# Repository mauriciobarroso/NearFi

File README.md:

# NearFi
NearFi is a proximity Wi-Fi repeater based on ESP32-S2-WROOM module (ESP32-S2), ESP IDF framework and KiCAD

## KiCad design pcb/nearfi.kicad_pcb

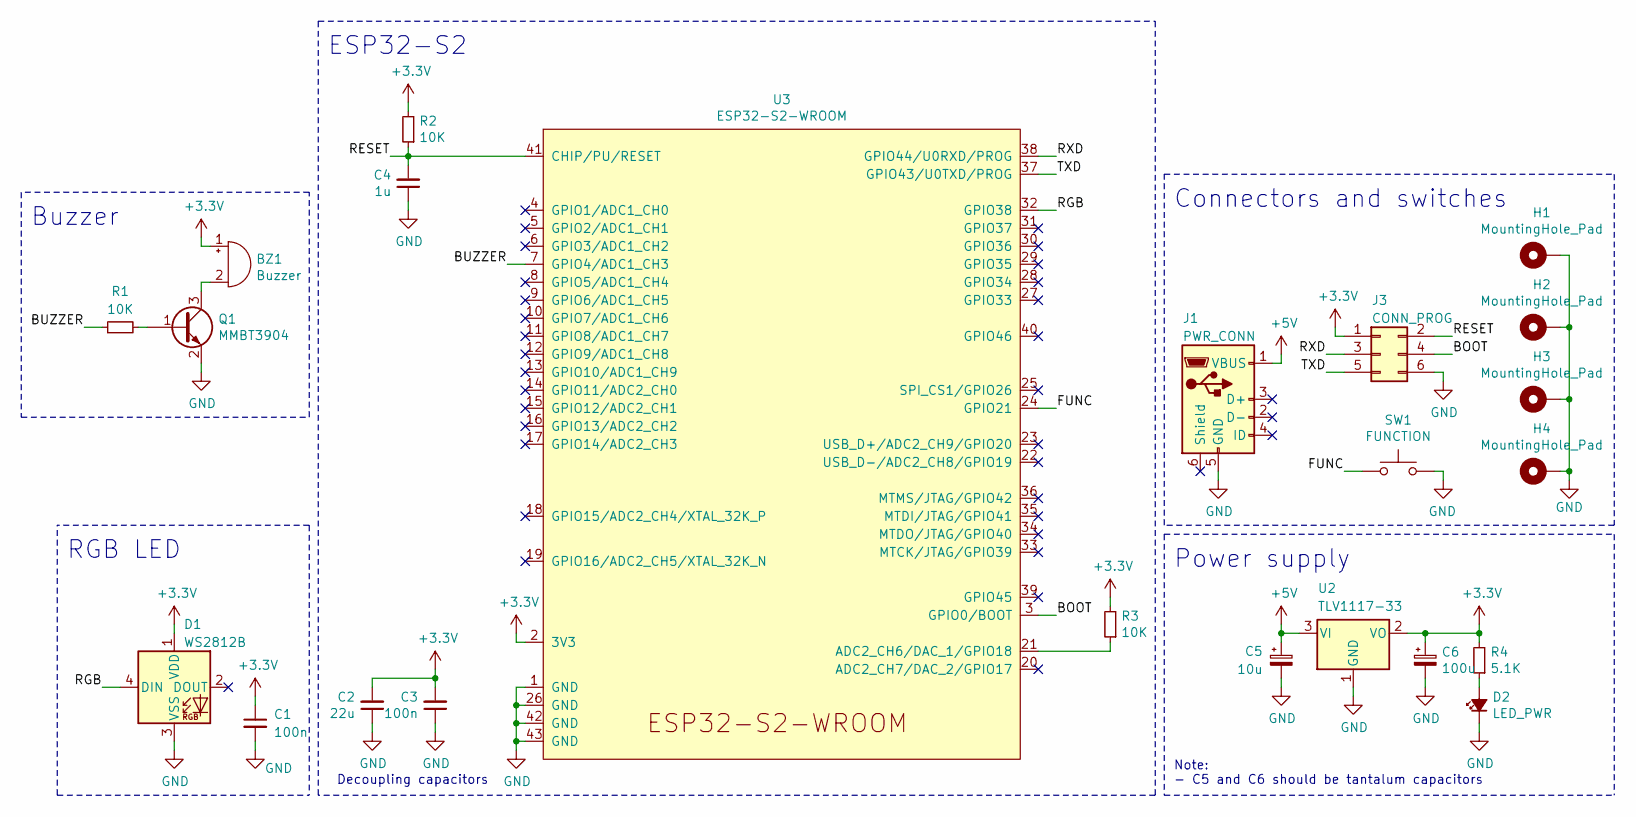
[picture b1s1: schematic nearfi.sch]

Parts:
BZ1: Buzzer; Buzzer_12x9.5RM7.6
C1, C3: 100n; C_0805_2012Metric_Pad1.18x1.45mm_HandSolder; LCSC C49678
C2: 22u; C_0805_2012Metric_Pad1.18x1.45mm_HandSolder; LCSC C45783
C4: 1u; C_0805_2012Metric_Pad1.18x1.45mm_HandSolder; LCSC C28323
C5: 10u; CP_EIA-3216-18_Kemet-A_Pad1.58x1.35mm_HandSolder; LCSC C7171
C6: 100u; CP_EIA-3528-21_Kemet-B_Pad1.50x2.35mm_HandSolder; LCSC C16133
D1: WS2812B; LED_WS2812B_PLCC4_5.0x5.0mm_P3.2mm; LCSC C2761795
D2: LED_PWR; LED_0805_2012Metric_Castellated; LCSC C84256
H1, H2, H3, H4: MountingHole_Pad; MountingHole_3.2mm_M3_Pad_Via
J1: PWR_CONN; USB_Micro-B_Molex_47346-0001; LCSC C132560
J3: CONN_PROG; PinHeader_2x03_P2.54mm_Vertical
Q1: MMBT3904; SOT-23; LCSC C20526
R1, R2, R3: 10K; R_0805_2012Metric_Pad1.20x1.40mm_HandSolder; LCSC C17414
R4: 5.1K; R_0805_2012Metric_Pad1.20x1.40mm_HandSolder; LCSC C27834
SW1: FUNCTION; SW_Tactile_SPST_Angled_PTS645Vx31-2LFS
U2: TLV1117-33; SOT-223-3_TabPin2; LCSC C37359
U3: ESP32-S2-WROOM; LCSC C967025

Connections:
+3V3: BZ1.1 (-), C1.1, C2.2, C3.2, C6.1, D1.1 (VDD), J3.1, R2.2, R3.2, R4.2, U2.2 (VO), U3.2 (3V3)
+5V: C5.1, J1.1 (VBUS), U2.3 (VI)
/BOOT: J3.4, U3.3 (GPIO0/BOOT)
/BUZZER: R1.1, U3.7 (GPIO4/ADC1_CH3)
/FUNC: SW1.2, U3.24 (GPIO21)
/RESET: C4.2, J3.2, R2.1, U3.41 (CHIP/PU/RESET)
/RGB: D1.4 (DIN), U3.32 (GPIO38)
/RXD: J3.3, U3.38 (GPIO44/U0RXD/PROG)
/TXD: J3.5, U3.37 (GPIO43/U0TXD/PROG)
GND: C1.2, C2.1, C3.1, C4.1, C5.2, C6.2, D1.3 (VSS), D2.1 (K), H1.1, H2.1, H3.1, H4.1, J1.5 (GND), J3.6, Q1.2 (E), SW1.1, U2.1 (GND), U3.1 (GND), U3.26 (GND), U3.42 (GND), U3.43 (GND)
unnamed: BZ1.2 (+), Q1.3 (C)
unnamed: D2.2 (A), R4.1
unnamed: Q1.1 (B), R1.2
unnamed: R3.1, U3.21 (ADC2_CH6/DAC_1/GPIO18)

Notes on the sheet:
RGB LED
Buzzer
Power supply
Note: - C5 and C6 should be tantalum capacitors
Connectors and switches
ESP32-S2
Decoupling capacitors

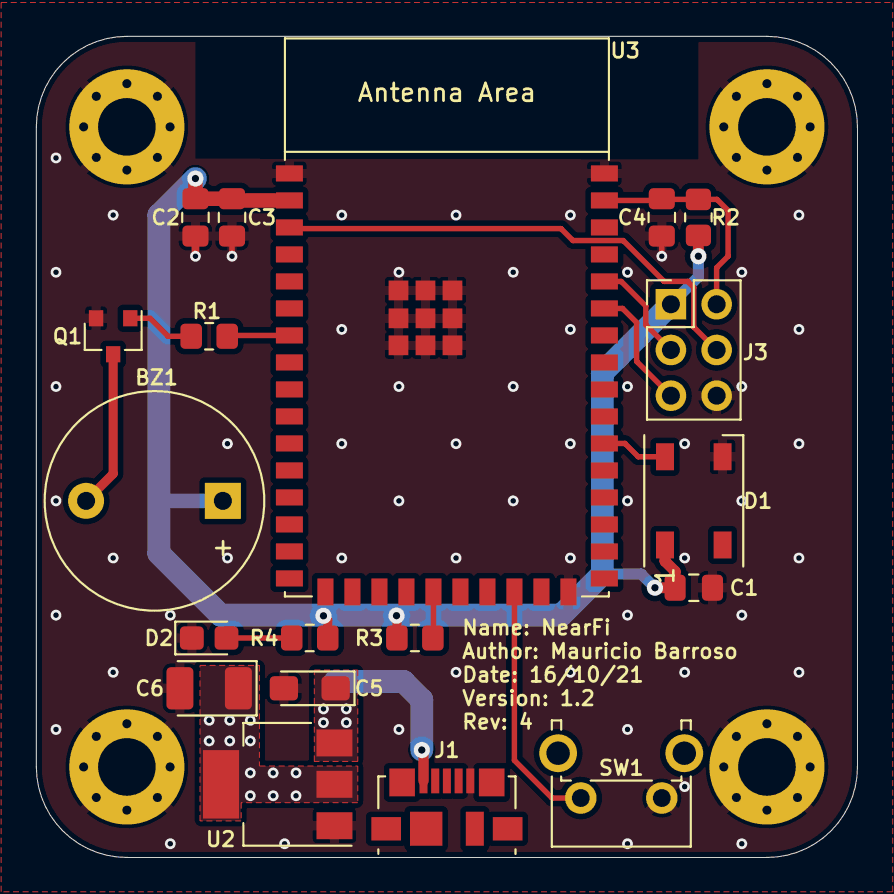
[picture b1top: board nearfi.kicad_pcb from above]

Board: 2 copper layers, 45.6 x 45.6 mm, 23 parts (0 on the bottom side), 14 nets.

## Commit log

2022-01-16 added code
2022-01-16 added pcb
2022-01-16 changed project name
2022-03-27 updated README.md file
